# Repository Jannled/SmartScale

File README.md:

> [!TIP]
> Archived, since I created a [second version](https://github.com/Jannled/SmartScale2) of this project

# SmartScale
Modification of a kitchen scale with an ESP32 and a HX711 on a custom PCB

# Software
For the development of this project, PlatformIO and KiCad were used.

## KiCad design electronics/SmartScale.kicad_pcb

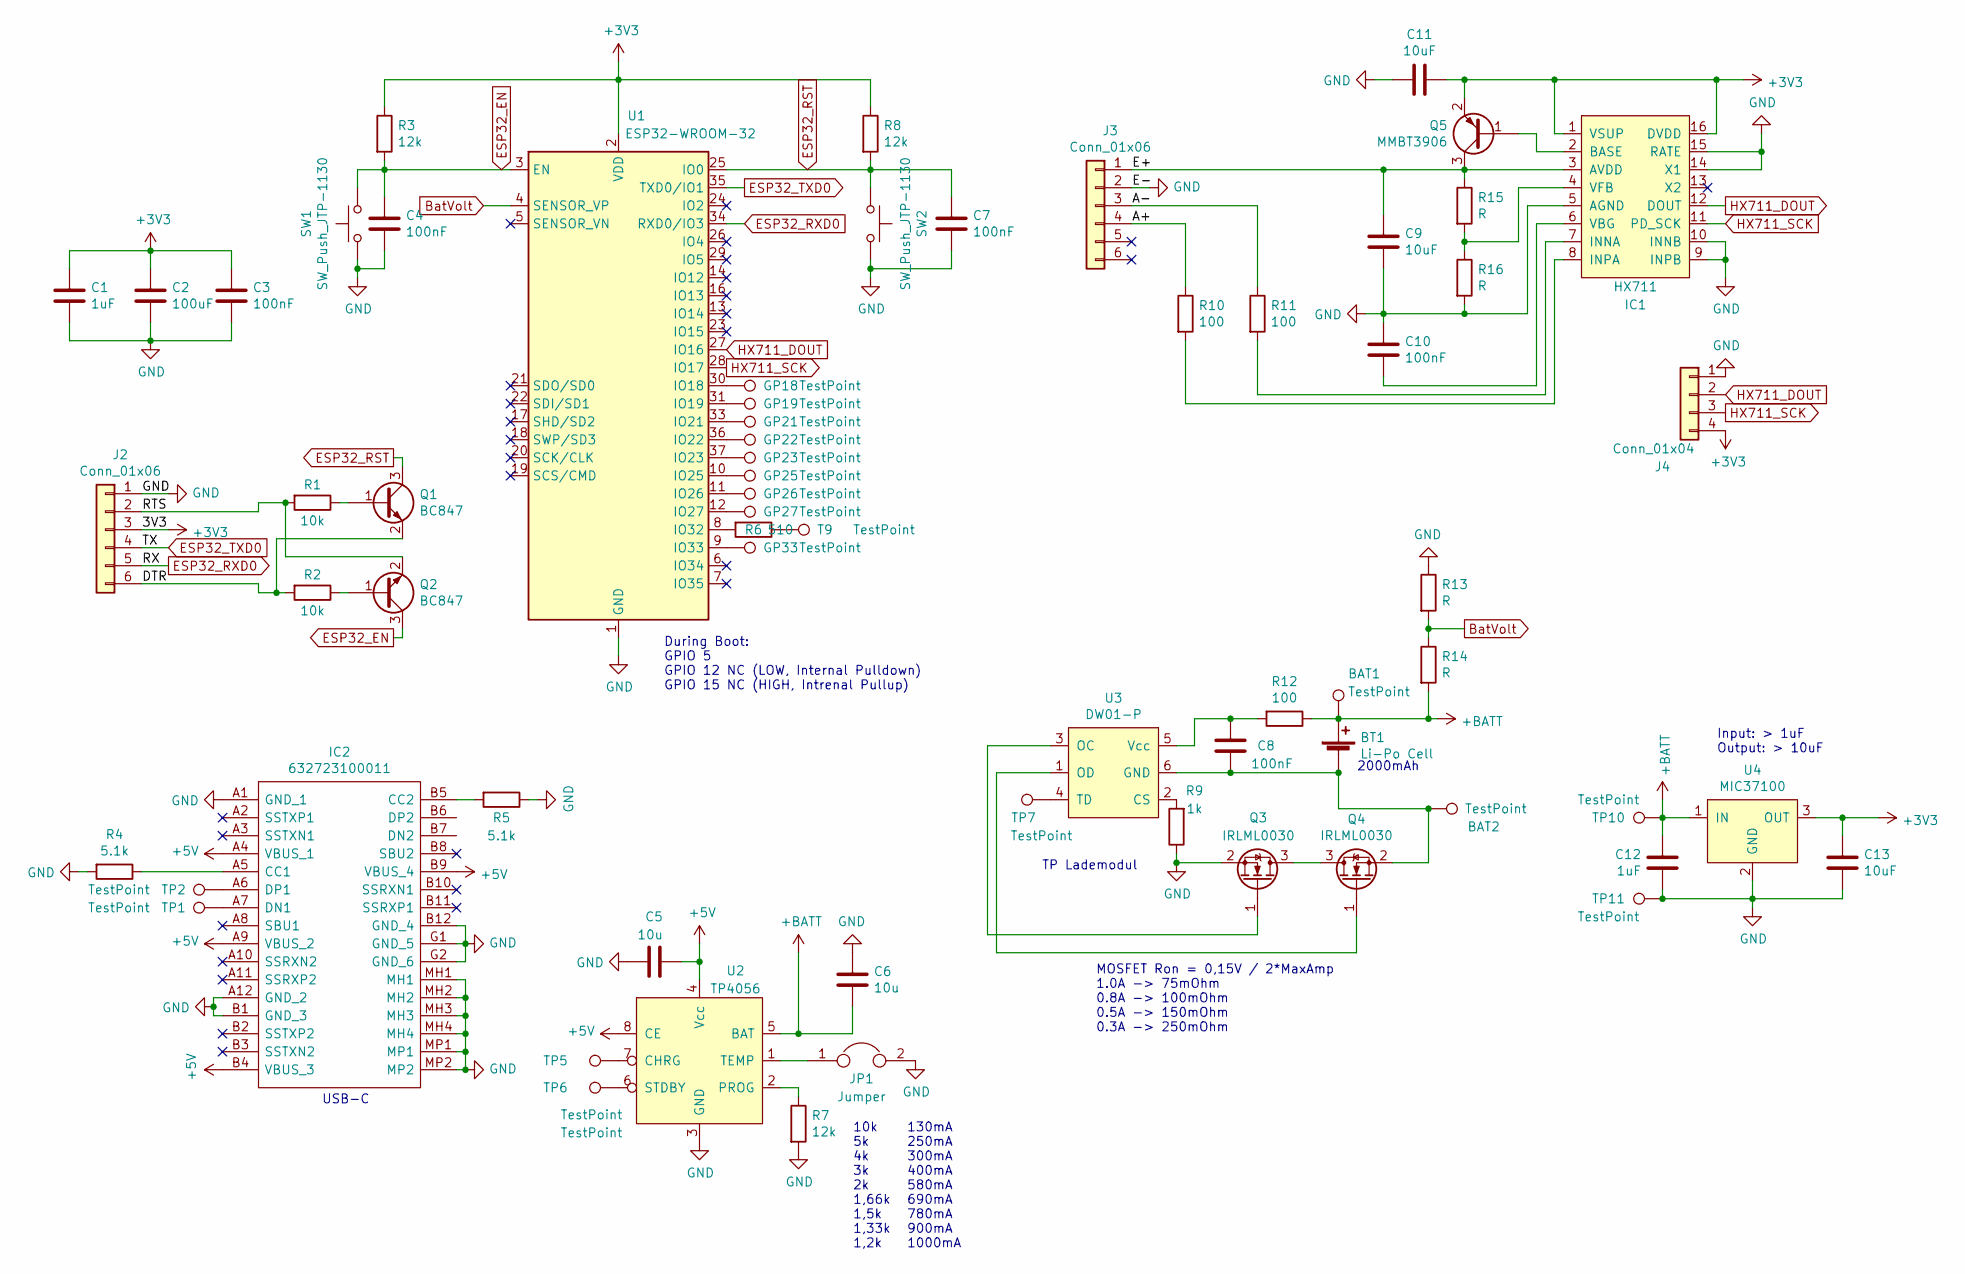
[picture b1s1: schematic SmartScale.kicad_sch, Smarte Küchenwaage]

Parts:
BAT1, BAT2: TestPoint; PinHeader_1x01_P2.54mm_Vertical
BT1: Li-Po Cell; D_1206_3216Metric_Castellated
C1, C12: 1uF; C_0805_2012Metric_Pad1.18x1.45mm_HandSolder
C2: 100uF; C_0805_2012Metric_Pad1.18x1.45mm_HandSolder
C3, C4, C7, C8, C10: 100nF; C_0805_2012Metric_Pad1.18x1.45mm_HandSolder
C5, C6: 10u; C_0805_2012Metric_Pad1.18x1.45mm_HandSolder
C9, C11, C13: 10uF; C_0805_2012Metric_Pad1.18x1.45mm_HandSolder
GP18, GP19, GP21, GP22, GP23, GP25, GP26, GP27, GP33: TestPoint; Pin_D0.7mm_L6.5mm_W1.8mm_FlatFork
IC1: HX711; SOP-16_4.4x10.4mm_P1.27mm
IC2: 632723100011; Mouser Part Number 710-632723100011
J2: Conn_01x06; PinHeader_1x06_P2.54mm_Horizontal
J3: Conn_01x06; PinSocket_1x06_P2.54mm_Vertical
J4: Conn_01x04; PinHeader_1x04_P2.54mm_Vertical
JP1: Jumper; SolderJumper-2_P1.3mm_Bridged_Pad1.0x1.5mm
Q1, Q2: BC847; SOT-23
Q3, Q4: IRLML0030; SOT-23
Q5: MMBT3906; SOT-23
R1, R2: 10k; R_0805_2012Metric_Pad1.20x1.40mm_HandSolder
R3, R7, R8: 12k; R_0805_2012Metric_Pad1.20x1.40mm_HandSolder
R4, R5: 5.1k; R_0805_2012Metric_Pad1.20x1.40mm_HandSolder
R6: 510; R_0805_2012Metric_Pad1.20x1.40mm_HandSolder
R9: 1k; R_0805_2012Metric_Pad1.20x1.40mm_HandSolder
R10, R11, R12: 100; R_0805_2012Metric_Pad1.20x1.40mm_HandSolder
R13, R14, R15, R16: R; R_0805_2012Metric_Pad1.20x1.40mm_HandSolder
SW1, SW2: SW_Push_JTP-1130; SolderJumper-2_P1.3mm_Open_RoundedPad1.0x1.5mm
T9: TestPoint; Pin_D0.7mm_L6.5mm_W1.8mm_FlatFork
TP1, TP2, TP5, TP6, TP7: TestPoint; TestPoint_Pad_D1.0mm
TP10, TP11: TestPoint; PinSocket_1x01_P2.54mm_Vertical
U1: ESP32-WROOM-32
U2: TP4056; SOP-8_3.9x4.9mm_P1.27mm
U3: DW01-P; SOT-23-6
U4: MIC37100; SOT-223

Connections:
+3V3: C1.1, C2.1, C3.1, C11.1, C13.1, IC1.1 (VSUP), IC1.16 (DVDD), J2.3, J4.4, Q5.2 (E), R3.1, R8.1, U1.2 (VDD), U4.3 (OUT)
+5V: C5.2, IC2.A4 (VBUS_1), IC2.A9 (VBUS_2), IC2.B4 (VBUS_3), IC2.B9 (VBUS_4), U2.4 (Vcc), U2.8 (CE); also elsewhere on the board
+BATT: BAT1.1, BT1.1 (+), C6.2, C12.2, R12.1, R14.2, TP10.1, U2.5 (BAT), U4.1 (IN)
/A+: J3.4, R10.1
/A-: J3.3, R11.1
/DTR: J2.6, Q1.2 (E), R2.2
/E+: C9.1, IC1.3 (AVDD), J3.1, Q5.3 (C), R15.1
/RTS: J2.2, Q2.2 (E), R1.2
BatVolt: R13.2, R14.1, U1.4 (SENSOR_VP)
ESP32_EN: C4.1, Q2.3 (C), R3.2, SW1.2, U1.3 (EN)
ESP32_RST: C7.1, Q1.3 (C), R8.2, SW2.2, U1.25 (IO0)
ESP32_RXD0: J2.5, U1.34 (RXD0/IO3)
ESP32_TXD0: J2.4, U1.35 (TXD0/IO1)
GND: C1.2, C2.2, C3.2, C4.2, C5.1, C6.1, C7.2, C9.2, C10.1, C11.2, C12.1, C13.2, IC1.5 (AGND), IC1.9 (INPB), IC1.10 (INNB), IC1.14 (X1), IC1.15 (RATE), IC2.A1 (GND_1), IC2.A12 (GND_2), IC2.B1 (GND_3), IC2.B12 (GND_4), IC2.G1 (GND_5), IC2.G2 (GND_6), IC2.MH1, IC2.MH2, IC2.MH3, IC2.MH4, IC2.MP1, IC2.MP2, J2.1, J3.2, J4.1, JP1.2, Q3.2 (S), R4.2, R5.1, R7.2, R9.1, R13.1, R16.2, SW1.1, SW2.1, TP11.1, U1.1 (GND), U1.15 (GND), U1.38 (GND), U1.39 (GND), U2.3 (GND), U4.2 (GND); also elsewhere on the board
HX711_DOUT: IC1.12 (DOUT), J4.2, U1.27 (IO16)
HX711_SCK: IC1.11 (PD_SCK), J4.3, U1.28 (IO17)
unnamed: BAT2.1, BT1.2 (-), C8.1, Q4.2 (S), U3.6 (GND)
unnamed: C8.2, R12.2, U3.5 (Vcc)
unnamed: C10.2, IC1.6 (VBG)
unnamed: GP18.1, U1.30 (IO18)
unnamed: GP19.1, U1.31 (IO19)
unnamed: GP21.1, U1.33 (IO21)
unnamed: GP22.1, U1.36 (IO22)
unnamed: GP23.1, U1.37 (IO23)
unnamed: GP25.1, U1.10 (IO25)
unnamed: GP26.1, U1.11 (IO26)
unnamed: GP27.1, U1.12 (IO27)
unnamed: GP33.1, U1.9 (IO33)
unnamed: IC1.2 (BASE), Q5.1 (B)
unnamed: IC1.4 (VFB), R15.2, R16.1
unnamed: IC1.7 (INNA), R11.2
unnamed: IC1.8 (INPA), R10.2
unnamed: IC2.A5 (CC1), R4.1
unnamed: IC2.A6 (DP1), TP2.1
unnamed: IC2.A7 (DN1), TP1.1
unnamed: IC2.B5 (CC2), R5.2
unnamed: JP1.1, U2.1 (TEMP)
unnamed: Q1.1 (B), R1.1
unnamed: Q2.1 (B), R2.1
unnamed: Q3.1 (G), U3.3 (OC)
unnamed: Q3.3 (D), Q4.3 (D)
unnamed: Q4.1 (G), U3.1 (OD)
unnamed: R6.1, T9.1
unnamed: R6.2, U1.8 (IO32)
unnamed: R7.1, U2.2 (PROG)
unnamed: R9.2, U3.2 (CS)
unnamed: TP5.1, U2.7 (CHRG)
unnamed: TP6.1, U2.6 (STDBY)
unnamed: TP7.1, U3.4 (TD)

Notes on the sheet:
TP Lademodul
USB-C
During Boot: GPIO 5 GPIO 12 NC (LOW, Internal Pulldown) GPIO 15 NC (HIGH, Intrenal Pullup)
MOSFET Ron = 0,15V / 2*MaxAmp 1.0A -> 75mOhm 0.8A -> 100mOhm 0.5A -> 150mOhm 0.3A -> 250mOhm
Input: > 1uF Output: > 10uF
130mA 250mA 300mA 400mA 580mA 690mA 780mA 900mA 1000mA
10k 5k 4k 3k 2k 1,66k 1,5k 1,33k 1,2k
2000mAh

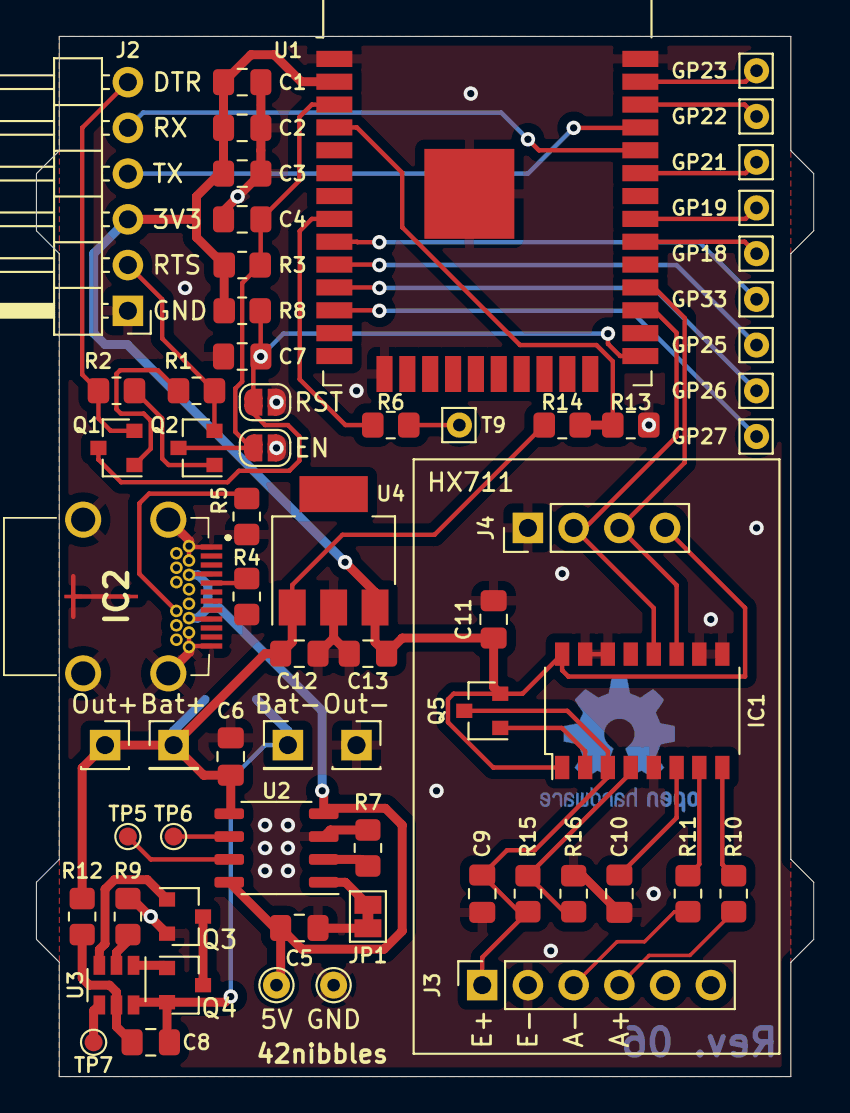
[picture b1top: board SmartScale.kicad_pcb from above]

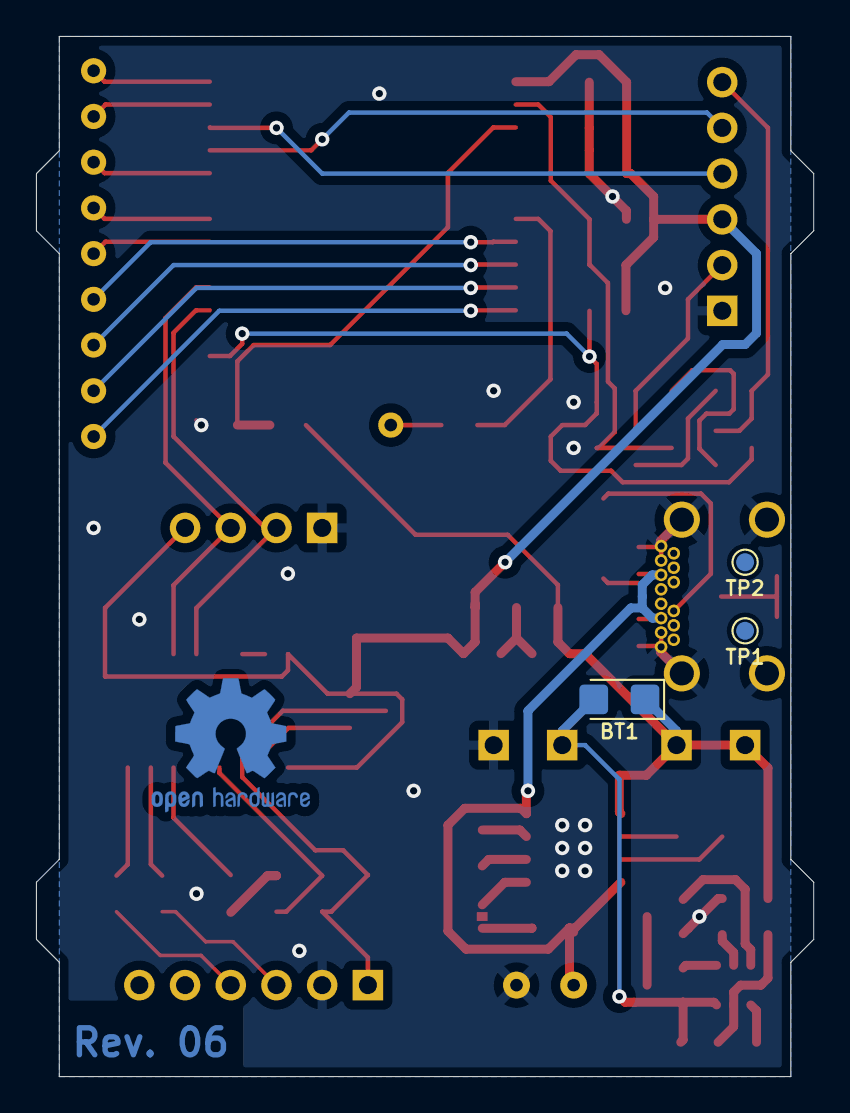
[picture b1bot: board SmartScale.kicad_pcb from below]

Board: 2 copper layers, 43.2 x 57.8 mm, 68 parts (3 on the bottom side), 49 nets.

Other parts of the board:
5V: TestPoint_THTPad_D1.5mm_Drill0.7mm
GND: TestPoint_THTPad_D1.5mm_Drill0.7mm

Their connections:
+5V: 5V.1; also elsewhere on the board
GND: GND.1; also elsewhere on the board

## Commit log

2021-10-19 Publish
2021-10-21 Menu config over serial. Next up Webserver
2021-10-23 Webserver, Next up Websockets
2021-10-23 Refactoring/restructuring
2021-10-23 Bloody hell why is my serial output appearing on the website
2021-10-24 Websocket works
2021-10-24 Got EEPROM to work
2021-10-24 Print precise divider
2021-10-25 Push PCB
2021-12-02 Pushed casing and updated PCB
2021-12-15 PCB Rev 5
    - Added 42Nibbles QR Code
    - Moved 5V connection
2022-01-19 Pushing changes made at my University
2022-03-23 PCB Rev 6, fixed error with flashing
2022-07-12 Intermediate push, dunno what I just broke but whatever
2023-05-09 Push after a long time
2023-05-09 Add HTML config interface
2023-05-16 Improve ui
2023-05-16 Add Touch
2023-05-16 Add HotSpot
2023-05-17 Try to fix WiFi AP
2023-05-23 hallo
2023-05-26 Add some Doc Links
2026-05-04 Update README.md
    Add an archive note
